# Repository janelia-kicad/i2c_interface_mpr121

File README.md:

# i2c_interface_mpr121

Authors:

    Peter Polidoro <polidorop@janelia.hhmi.org>

License:

    BSD

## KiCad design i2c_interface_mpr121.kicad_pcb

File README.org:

#+TITLE: i2c_interface_mpr121
#+AUTHOR: Peter Polidoro
#+EMAIL: peter@polidoro.io

* Repository Information
  - Author :: Peter Polidoro
  - License :: Open-Source Hardware

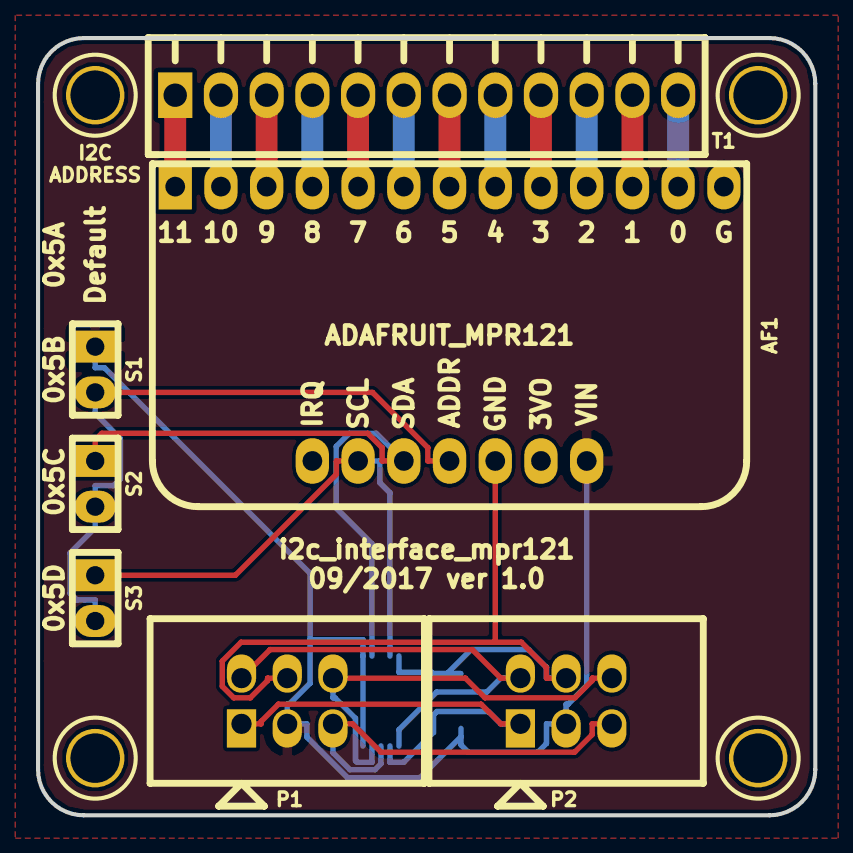
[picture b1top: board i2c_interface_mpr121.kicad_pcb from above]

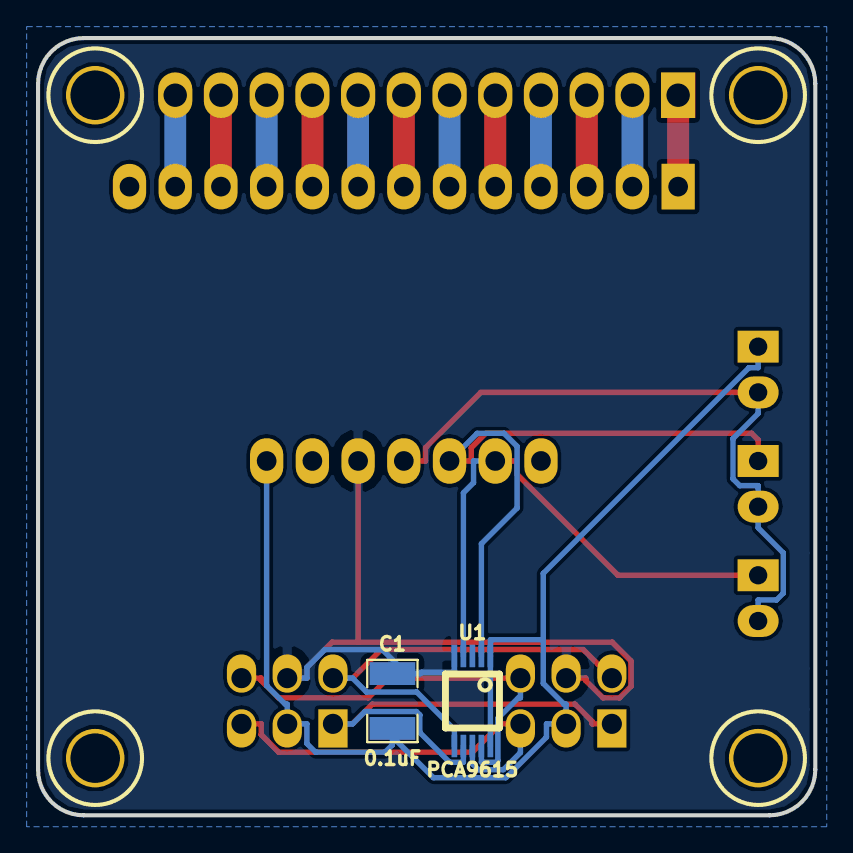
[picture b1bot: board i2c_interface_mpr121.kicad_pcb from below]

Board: 2 copper layers, 43.2 x 43.2 mm, 13 parts (2 on the bottom side), 21 nets.

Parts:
AF1: ADAFRUIT_MPR121
C1: 0.1uF; SM1210
P1, P2: HEADER_02X03; HEADER_02x03
S1, S2, S3: HEADER_01X02; HEADER_01x02
SO1, SO2, SO3, SO4: STANDOFF_M2.5x0.45x8; MOUNTING_HOLE_M2.5
T1: TERM_BLK_12_PIN_0.1_PITCH
U1: PCA9615; TSSOP10

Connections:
/ADDR: AF1.17, S1.2, S2.2, S3.2
/DSCLM: P1.2, P2.2, U1.6
/DSCLP: P1.1, P2.1, U1.7
/DSDAM: P1.6, P2.6, U1.9
/DSDAP: P1.5, P2.5, U1.8
/IN_0: AF1.12, T1.12
/IN_1: AF1.11, T1.11
/IN_2: AF1.10, T1.10
/IN_3: AF1.9, T1.9
/IN_4: AF1.8, T1.8
/IN_5: AF1.7, T1.7
/IN_6: AF1.6, T1.6
/IN_7: AF1.5, T1.5
/IN_8: AF1.4, T1.4
/IN_9: AF1.3, T1.3
/IN_10: AF1.2, T1.2
/IN_11: AF1.1, T1.1
/SCL: AF1.19, S3.1, U1.4
/SDA: AF1.18, S2.1, U1.2
GND: AF1.16, C1.2, P1.4, P2.4, U1.5
VEE: AF1.14, C1.1, P1.3, P2.3, S1.1, U1.1, U1.10

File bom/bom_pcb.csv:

Item,Reference(s),Value,Quantity,Description,PartNumber,Vendor
1,AF1,ADAFRUIT_MPR121,1,MPR121 TOUCH SENSE 12-KEY,1528-1038-ND,digikey
2,C1,0.1uF,1,CAP CER 0.1UF 50V 10% X7R 1210,399-13229-1-ND,digikey
3,P1 P2,HEADER_02X03,2,CONN HEADER 6POS 2.54,732-5394-ND,digikey
4,S1 S2 S3,HEADER_01X02,3,CONN HEADER 2POS .100 VERT GOLD,609-3500-ND,digikey
5,SO1 SO2 SO3 SO4,STANDOFF_M2.5x0.45x8,4,HEX STANDOFF M2.5 ALUMINUM 8MM,36-24422-ND,digikey
6,T1,TERM_BLK_12_PIN_0.1_PITCH,1,CONN TERM BLOCK 2.54MM 12POS PCB, ED10568-ND,digikey
7,U1,PCA9615,1,IC REDRIVER I2C 2CH 10TSSOP,568-11484-1-ND,digikey

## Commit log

2017-09-19 Initial commit.
2017-09-19 Added footprints.
2017-09-21 Progress towards v1.0.
2017-09-22 Added 2 pin header.
2017-09-22 Removed extra libraries.
2017-09-22 Finished v1.0.
2018-01-08 Updated to v4.
2018-01-08 Added v4 files.
2018-01-08 Updated gitignore.
2018-03-09 Update license from software to hardware.
2018-04-12 README.md -> README.org.
2018-04-19 Added .DS_Store to .gitignore.
2018-05-16 Added generate_kicad_documentation submodule.
2018-05-17 Updated submodules.
2018-08-12 Removed v4 files.
2018-08-24 Removed F.SilkS from pads.
2021-09-16 Update email address
2021-09-21 Remove ignored files
2022-02-22 Add guix files
2022-02-23 Add guix documentation
2024-05-31 Add board image
